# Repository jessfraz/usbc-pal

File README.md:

# usbc-pal

This is a slighly modified version of [pd-buddy](https://git.clarahobbs.com/pd-buddy/pd-buddy-sink).

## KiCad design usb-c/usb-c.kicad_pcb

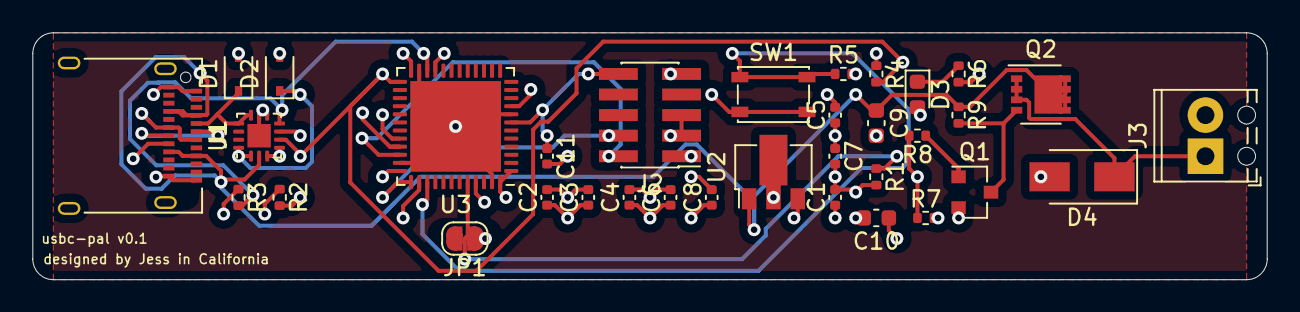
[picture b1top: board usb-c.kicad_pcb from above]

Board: 4 copper layers, 76.2 x 15.2 mm, 34 parts (0 on the bottom side), 21 nets.

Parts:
C1, C2, C3, C4, C5, C6, C11: 0.1μF; C_0402_1005Metric
C7, C8: 1μF; C_0402_1005Metric
C9: 1μF; C_0603_1608Metric
C10: 2.2μF; C_0603_1608Metric
D1: MM325V6T1G; D_SOD-323
D2: MM3Z5V6T1G; D_SOD-323
D3: STATUS_LED; LED_0603_1608Metric
D4: B140-E3; D_SMA
J1: USB_C; USB_C_Receptacle_Amphenol_12401610E4-2A
J2: SWD; PinHeader_2x05_P1.27mm_Vertical_SMD
J3: OUTPUT; TerminalBlock_Phoenix_MPT-0,5-2-2.54_1x02_P2.54mm_Horizontal
JP1: JUMPER; SolderJumper-2_P1.3mm_Open_RoundedPad1.0x1.5mm
Q1: MMBT3904; SOT-23
Q2: DMP3017SFG; Diodes_PowerDI3333-8
R1, R5, R7: 10kΩ; R_0402_1005Metric
R2, R3, R4, R8: 2kΩ; R_0402_1005Metric
R6: 220kΩ; R_0402_1005Metric
R9: 100kΩ; R_0402_1005Metric
SW1: SWITCH; SW_SPST_PTS810
U1: FUSB302B11MPX; WQFN-14-1EP_2.5x2.5mm_P0.5mm_EP1.45x1.45mm
U2: AP2204R-3.3; SOT-89-3
U3: STM32F072C8Ux; QFN-48-1EP_7x7mm_P0.5mm_EP5.6x5.6mm

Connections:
+3V3: C1.1, C2.1, C3.1, C4.1, C5.1, C6.1, C7.1, C8.1, C10.1, J2.1, JP1.1, R2.1, R3.1, R4.1, SW1.2, U1.3, U1.4, U2.3, U3.1, U3.9, U3.24, U3.36, U3.48
/BOOT: JP1.2, R1.1, U3.44
/SETUP: R5.1, SW1.1, U3.39
/SWCLK: J2.4, U3.37
/SWDIO: J2.2, U3.34
/nRST: C11.1, J2.10, U3.7
D+: J1.A6, J1.B6, U3.33
D-: J1.A7, J1.B7, U3.32
GND: C1.2, C2.2, C3.2, C4.2, C5.2, C6.2, C7.2, C8.2, C9.2, C10.2, C11.2, D1.2, D2.2, D4.2, J1.A1, J1.A12, J1.B1, J1.B12, J1.S1, J2.3, J2.5, J2.9, J3.2, Q1.2, R1.2, R5.2, R6.2, R7.2, U1.8, U1.9, U1.15, U2.2, U3.8, U3.23, U3.35, U3.47, U3.49
INT_N: R4.2, U1.5, U3.25
unnamed: D1.1, J1.A5, U1.10, U1.11
unnamed: D2.1, J1.B5, U1.1, U1.14
unnamed: D3.1, R6.1
unnamed: D3.2, U3.38
unnamed: D4.1, J3.1, Q2.1, Q2.2, Q2.3
unnamed: Q1.1, R8.1
unnamed: Q1.3, Q2.4, R9.2
OUT_CTRL: R7.1, R8.2, U3.45
SCL: R2.2, U1.6, U3.21
SDA: R3.2, U1.7, U3.22
VBUS: C9.1, J1.A4, J1.A9, J1.B4, J1.B9, Q2.5, R9.1, U1.2, U2.1

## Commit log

2020-10-02 add datasheets
2020-10-02 update usb-dongle
2020-10-03 add FUSB302B datasheet
2020-10-03 update datasheets
2020-10-04 better design
2020-10-05 update dongle
2020-10-05 add image
2020-10-05 cleanup
2020-10-05 add rescure
2020-10-05 fix typo
